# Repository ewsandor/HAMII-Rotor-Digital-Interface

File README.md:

# HAMII Rotor Digital Interface 
An interface to control a CDE HAM II antenna rotor with a computer based on the Rotor-EZ protocol.

<p>
This project uses an Arduino Nano to control relays to position a CDE HAM II rotor.  The software for the rotor is included in the 'software' folder.
</p>

<p>
A schematic and PCB is included in the folder 'pcb'.  
The PCB depends on Eagle librarys provided by the following repositories:<br>
Arduino-Eagle-Cad-Library   -   https://github.com/cyberlink1/Arduino-Eagle-Cad-Library<br>
Maker-Tools-Eagle-Libraries  -   https://github.com/dvdnhm/Maker-Tools-Eagle-Libraries<br>
  -Error exists in Maker-Tools-Eagle-Libraries, NO and NC are reversed on relay schematic symbol. HAMII Rotor Digital Interface has corrected for this error 
 </p>

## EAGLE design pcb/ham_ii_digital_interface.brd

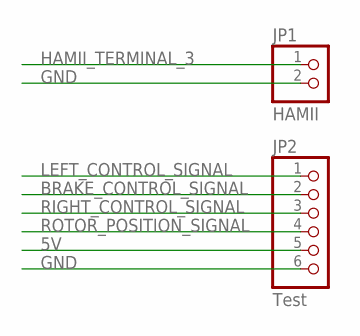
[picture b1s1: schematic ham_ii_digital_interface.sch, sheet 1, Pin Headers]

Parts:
JP1: HAMII; 1X02
JP2: Test; 1X06

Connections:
5V: JP2.5; also elsewhere on the board
BRAKE_CONTROL_SIGNAL: JP2.2; also elsewhere on the board
GND: JP1.2, JP2.6; also elsewhere on the board
HAMII_TERMINAL_3: JP1.1; also elsewhere on the board
LEFT_CONTROL_SIGNAL: JP2.1; also elsewhere on the board
RIGHT_CONTROL_SIGNAL: JP2.3; also elsewhere on the board
ROTOR_POSITION_SIGNAL: JP2.4; also elsewhere on the board

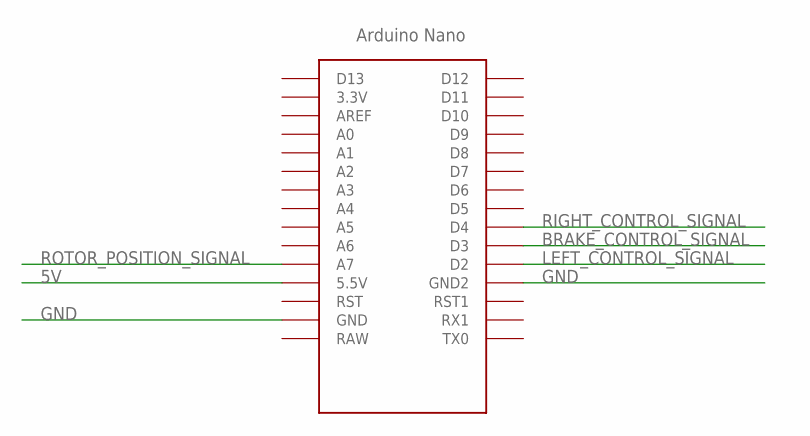
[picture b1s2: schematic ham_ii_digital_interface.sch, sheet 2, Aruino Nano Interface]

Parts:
U$1: NANO

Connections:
5V: U$1.5V (5.5V); also elsewhere on the board
BRAKE_CONTROL_SIGNAL: U$1.D3; also elsewhere on the board
GND: U$1.GND, U$1.GND1 (GND2); also elsewhere on the board
LEFT_CONTROL_SIGNAL: U$1.D2; also elsewhere on the board
RIGHT_CONTROL_SIGNAL: U$1.D4; also elsewhere on the board
ROTOR_POSITION_SIGNAL: U$1.A7; also elsewhere on the board

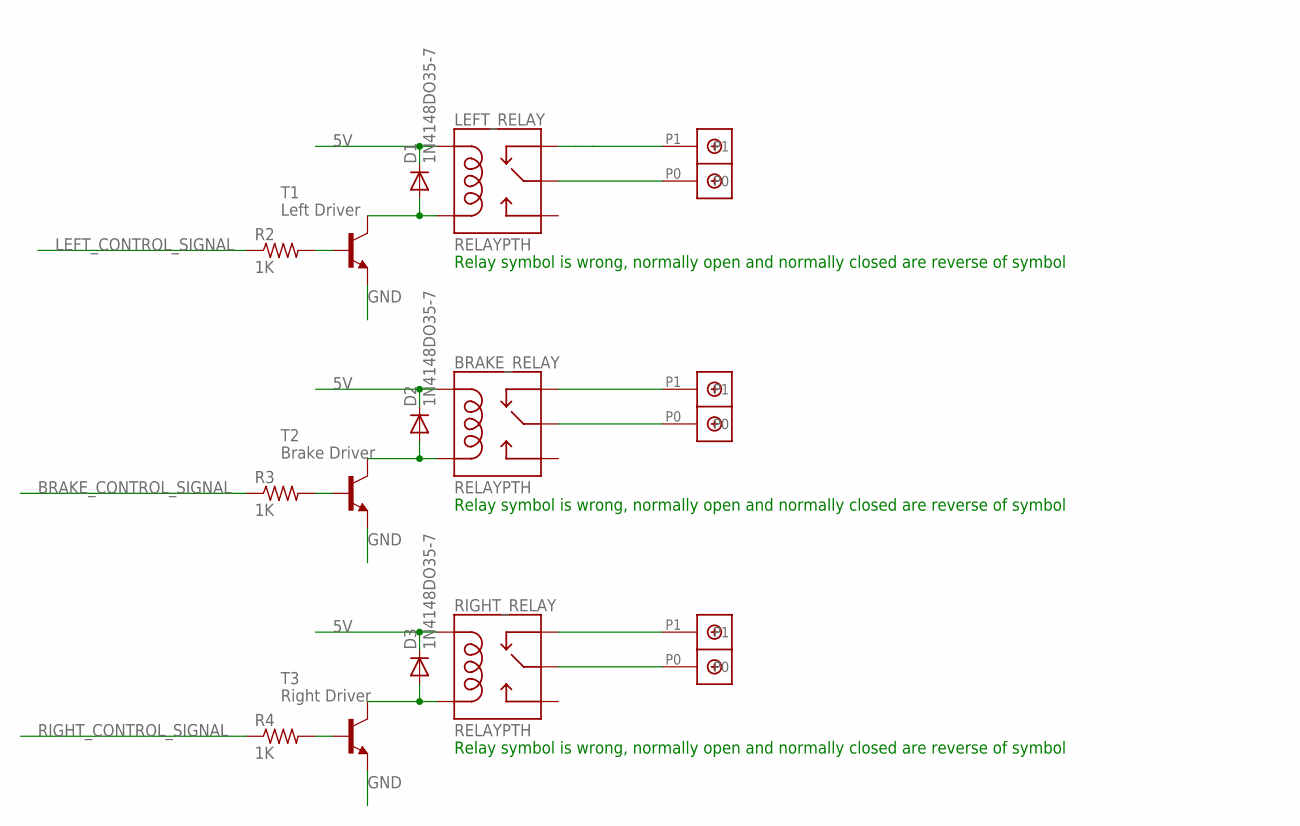
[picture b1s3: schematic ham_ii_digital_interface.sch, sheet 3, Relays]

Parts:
BRAKE_RELAY: RELAYPTH; SRD-05VDC-SL-C
D1, D2, D3: 1N4148DO35-7; DO35-7
LEFT_RELAY: RELAYPTH; SRD-05VDC-SL-C
R2, R3, R4: 1K; 0207/10
RIGHT_RELAY: RELAYPTH; SRD-05VDC-SL-C
T1: Left Driver; TO92
T2: Brake Driver; TO92
T3: Right Driver; TO92
U$5, U$6, U$7: DBCONN-1X2

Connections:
5V: BRAKE_RELAY.COIL1, D1.C, D2.C, D3.C, LEFT_RELAY.COIL1, RIGHT_RELAY.COIL1; also elsewhere on the board
BRAKE_CONTROL_SIGNAL: R3.1; also elsewhere on the board
GND: T1.1 (E), T2.1 (E), T3.1 (E); also elsewhere on the board
LEFT_CONTROL_SIGNAL: R2.1; also elsewhere on the board
unnamed: LEFT_RELAY.SWCOMMON, U$5.P0
unnamed: LEFT_RELAY.SWCLOSED (SWCLOSE), U$5.P1
unnamed: BRAKE_RELAY.SWCOMMON, U$6.P0
unnamed: BRAKE_RELAY.SWCLOSED (SWCLOSE), U$6.P1
unnamed: RIGHT_RELAY.SWCOMMON, U$7.P0
unnamed: RIGHT_RELAY.SWCLOSED (SWCLOSE), U$7.P1
unnamed: R2.2, T1.2 (B)
unnamed: R3.2, T2.2 (B)
unnamed: R4.2, T3.2 (B)
unnamed: D3.A, RIGHT_RELAY.COIL0, T3.3 (C)
unnamed: BRAKE_RELAY.COIL0, D2.A, T2.3 (C)
unnamed: D1.A, LEFT_RELAY.COIL0, T1.3 (C)
RIGHT_CONTROL_SIGNAL: R4.1; also elsewhere on the board

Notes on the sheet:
Relay symbol is wrong, normally open and normally closed are reverse of symbol

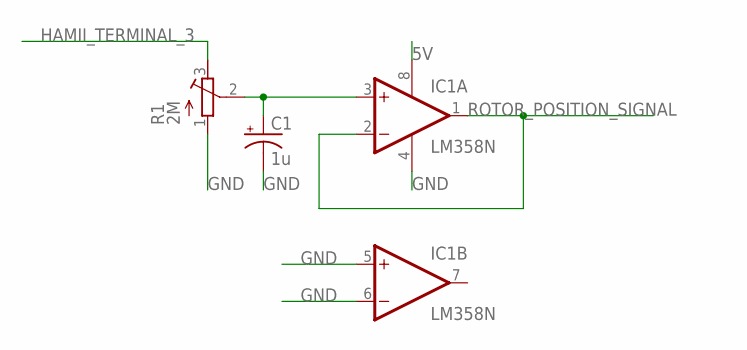
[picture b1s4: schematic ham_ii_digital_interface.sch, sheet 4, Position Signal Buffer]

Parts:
C1: 1u; E2-5
IC1: LM358N; DIL08
R1: 2M; RTRIM3296W

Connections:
5V: IC1.8 (V+); also elsewhere on the board
GND: C1.-, IC1.4 (V-), IC1.5 (+IN), IC1.6 (-IN), R1.1 (A); also elsewhere on the board
HAMII_TERMINAL_3: R1.3 (E); also elsewhere on the board
unnamed: C1.+, IC1.3 (+IN), R1.2 (S)
ROTOR_POSITION_SIGNAL: IC1.1 (OUT), IC1.2 (-IN); also elsewhere on the board

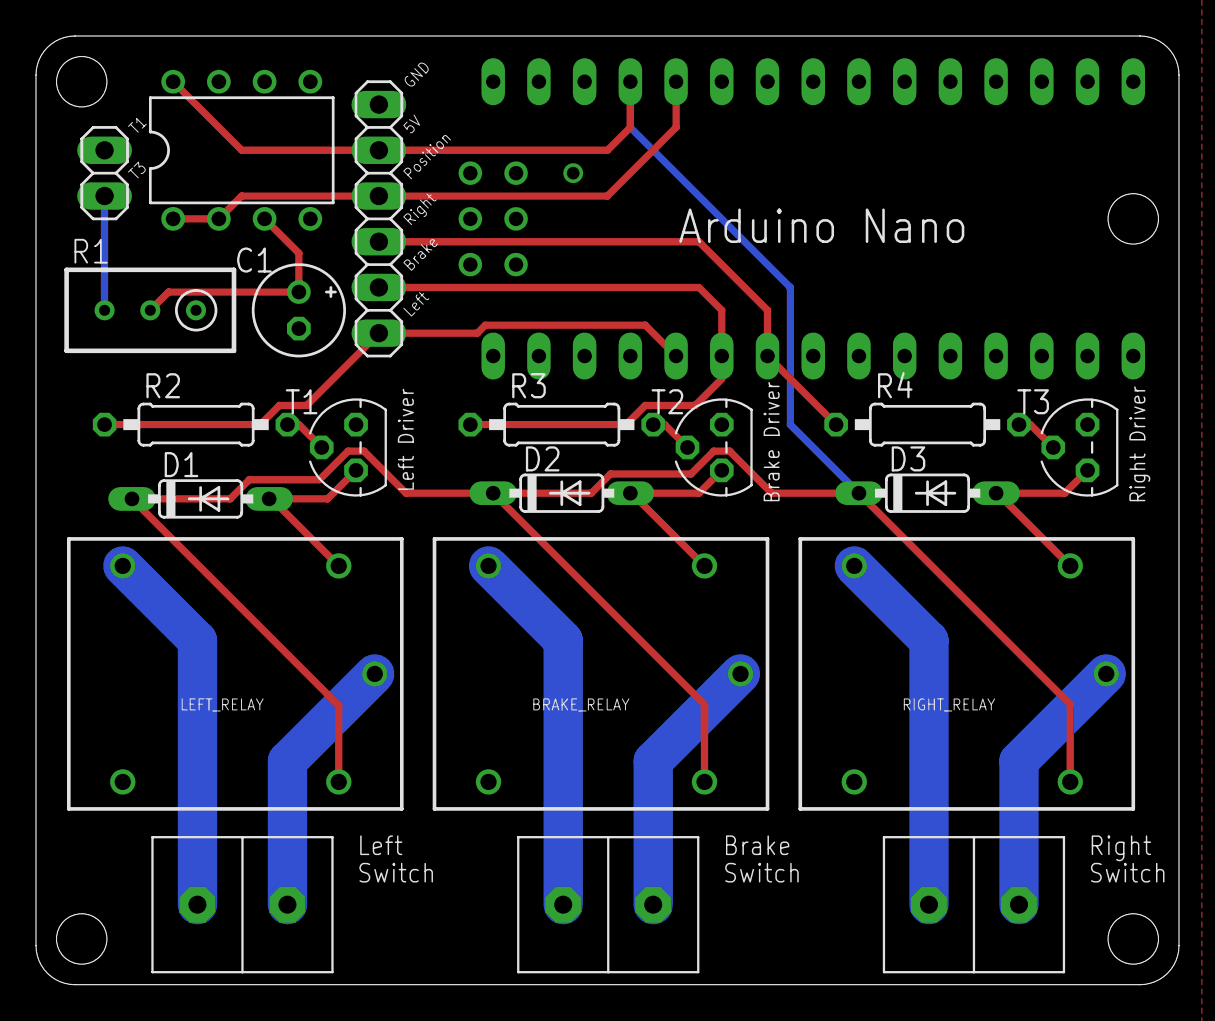
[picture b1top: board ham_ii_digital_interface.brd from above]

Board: 2 copper layers, 63.5 x 52.7 mm, 21 parts (0 on the bottom side), 20 nets.

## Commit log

2017-04-21 Set theme jekyll-theme-slate
2017-04-21 Initial upload of files into git repository
2017-04-23 Changed value of C1 and changed C1 to an electrolytic capacitor.
2017-04-23 Improved trace routing.
2017-04-23 Minor improvments before ordering first run
2017-05-05 Fixed issue discovered after receiving print of PCB. The NO and NC pins on the SRD-05VDC-SL-C schematic symbol are reveresed resulting in incorrect functionality. Trace must be cut on NC pin and a ju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
2017-05-05 Update README.md
    Added note about error in supporting library
